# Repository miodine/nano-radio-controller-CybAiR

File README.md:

# nano-radio-controller-CybAiR
Beginner electronics project - 433MHz &amp; 2.4GHz RC transmitter based on Arduino Nano board (Hardware layout + Software).
Designed and built as a part of the activity in CybAiR SC; Poznan University of Technology.

!

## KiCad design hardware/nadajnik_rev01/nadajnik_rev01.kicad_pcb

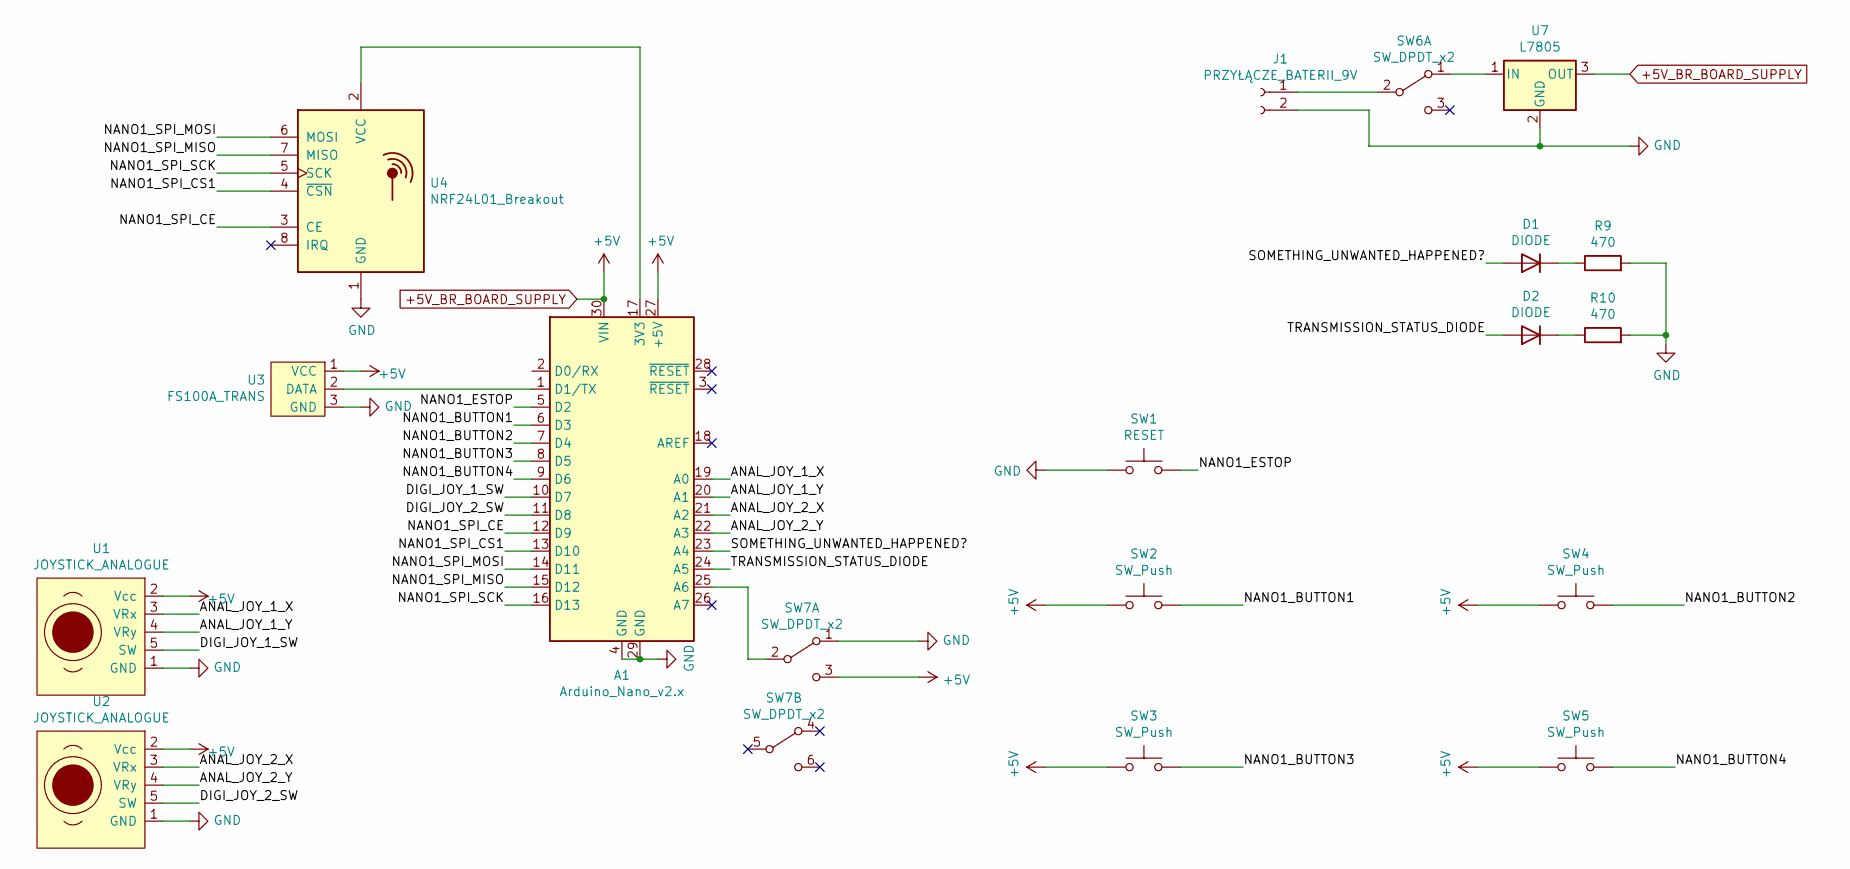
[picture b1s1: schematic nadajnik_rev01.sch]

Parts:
A1: Arduino_Nano_v2.x; Arduino_Nano
D1, D2: DIODE; LED_D3.0mm_IRGrey
J1: PRZYŁĄCZE_BATERII_9V; PinSocket_1x02_P2.54mm_Horizontal
R9, R10: 470; R_Axial_DIN0207_L6.3mm_D2.5mm_P10.16mm_Horizontal
SW1: RESET; SW_PUSH_6mm_H13mm
SW2, SW3, SW4, SW5: SW_Push; SW_PUSH_6mm_H13mm
SW6, SW7: SW_DPDT_x2; SW_CuK_JS202011AQN_DPDT_Angled
U1, U2: JOYSTICK_ANALOGUE; PinSocket_1x05_P2.54mm_Horizontal
U3: FS100A_TRANS; PinSocket_1x03_P2.54mm_Horizontal
U4: NRF24L01_Breakout; nRF24L01_Breakout
U7: L7805; TO-220-3_Horizontal_TabUp

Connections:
+5V_BR_BOARD_SUPPLY: A1.27 (+5V), A1.30 (VIN), SW2.1, SW3.1, SW4.1, SW5.1, SW7.3 (C), U1.2 (Vcc), U2.2 (Vcc), U3.1 (VCC), U7.3 (OUT)
/ANAL_JOY_1_X: A1.19 (A0), U1.3 (VRx)
/ANAL_JOY_1_Y: A1.20 (A1), U1.4 (VRy)
/ANAL_JOY_2_X: A1.21 (A2), U2.3 (VRx)
/ANAL_JOY_2_Y: A1.22 (A3), U2.4 (VRy)
/DIGI_JOY_1_SW: A1.10 (D7), U1.5 (SW)
/DIGI_JOY_2_SW: A1.11 (D8), U2.5 (SW)
/NANO1_BUTTON1: A1.6 (D3), SW2.2
/NANO1_BUTTON2: A1.7 (D4), SW4.2
/NANO1_BUTTON3: A1.8 (D5), SW3.2
/NANO1_BUTTON4: A1.9 (D6), SW5.2
/NANO1_ESTOP: A1.5 (D2), SW1.2
/NANO1_SPI_CE: A1.12 (D9), U4.3 (CE)
/NANO1_SPI_CS1: A1.13 (D10), U4.4 (~CSN)
/NANO1_SPI_MISO: A1.15 (D12), U4.7 (MISO)
/NANO1_SPI_MOSI: A1.14 (D11), U4.6 (MOSI)
/NANO1_SPI_SCK: A1.16 (D13), U4.5 (SCK)
/SOMETHING_UNWANTED_HAPPENED?: A1.23 (A4), D1.1 (A)
/TRANSMISSION_STATUS_DIODE: A1.24 (A5), D2.1 (A)
GND: A1.4 (GND), A1.29 (GND), J1.2, R9.2, R10.2, SW1.1, SW7.1 (A), U1.1 (GND), U2.1 (GND), U3.3 (GND), U4.1 (GND), U7.2 (GND)
unnamed: A1.1 (D1/TX), U3.2 (DATA)
unnamed: A1.17 (3V3), U4.2 (VCC)
unnamed: A1.25 (A6), SW7.2 (B)
unnamed: D1.2 (K), R9.1
unnamed: D2.2 (K), R10.1
unnamed: J1.1, SW6.2 (B)
unnamed: SW6.1 (A), U7.1 (IN)

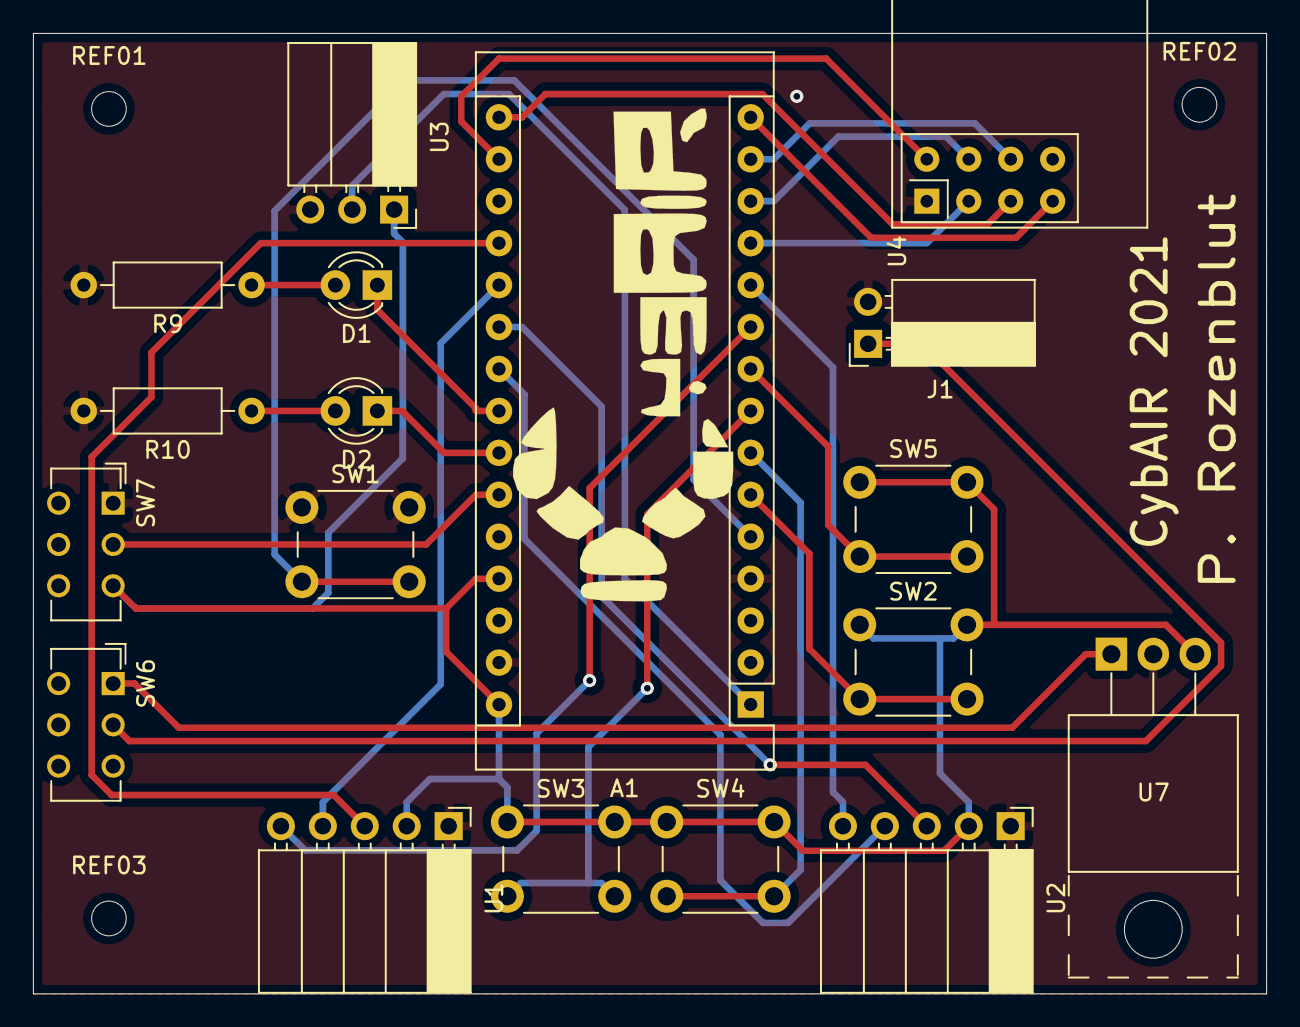
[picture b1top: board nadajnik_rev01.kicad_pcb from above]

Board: 2 copper layers, 74.7 x 58.2 mm, 21 parts (0 on the bottom side), 27 nets.

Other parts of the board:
REF01, REF02, REF03: MountingHole_2.1mm

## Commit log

2021-10-23 init
